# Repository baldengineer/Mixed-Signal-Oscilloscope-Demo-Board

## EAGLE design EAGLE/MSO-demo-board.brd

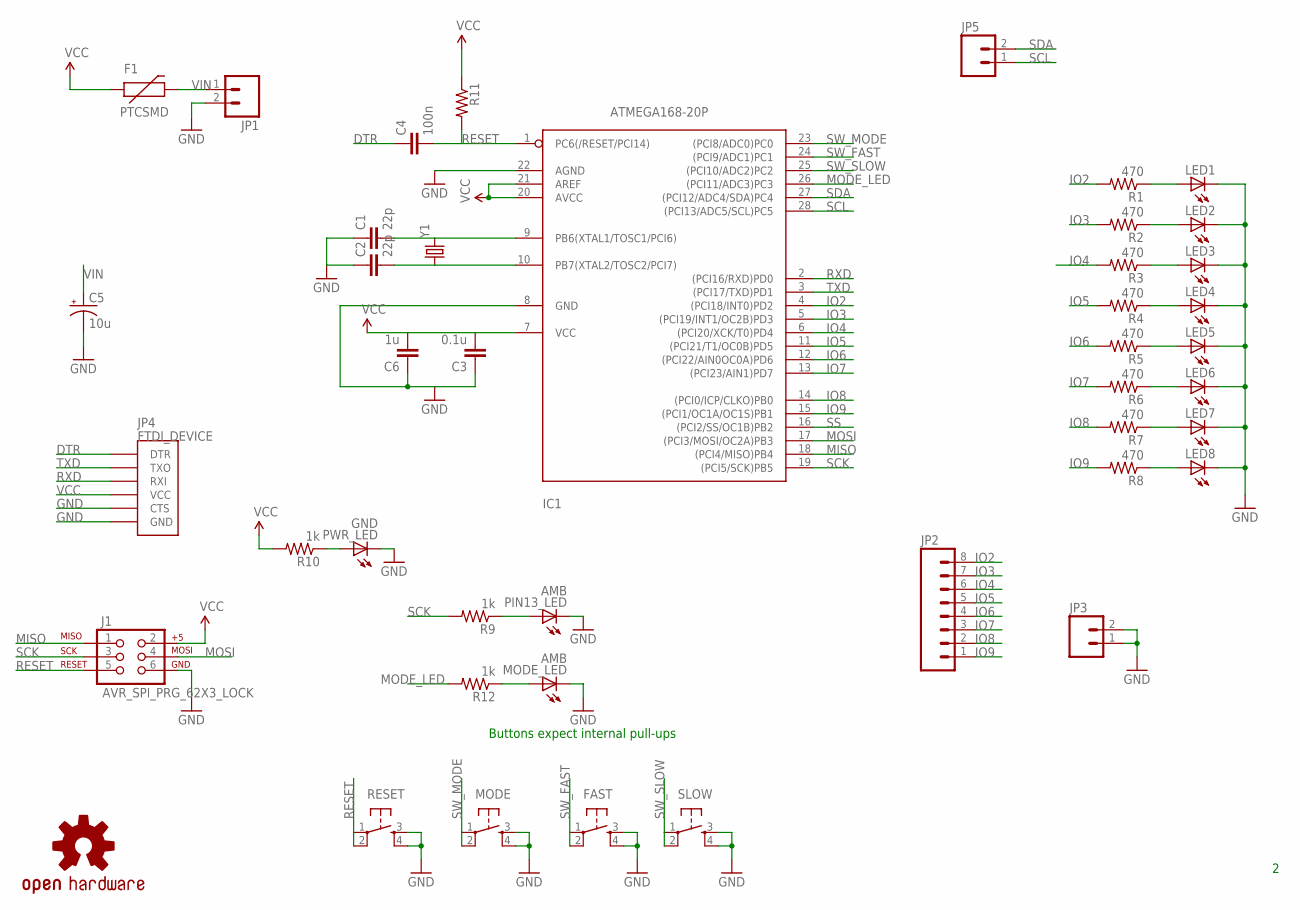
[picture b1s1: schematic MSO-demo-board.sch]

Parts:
C1, C2: 22p; 1206
C3: 0.1u; 1206
C4: 100n; 1206
C5: 10u; CT7343
C6: 1u; 1206
F1: PTCSMD; PTC-1206
FAST: TAC_SWITCHSMD; TACTILE_SWITCH_SMD
IC1: ATMEGA168-20P; DIL28-3
J1: AVR_SPI_PRG_62X3_LOCK; 2X3_LOCK
JP1, JP3, JP5: M02LOCK; 1X02_LOCK
JP2: M08LOCK; 1X08_LOCK
JP4: FTDI_DEVICE; FTDI_DEVICE_SIDE
LED1, LED2, LED3, LED4, LED5, LED6, LED7, LED8: LED1206; LED-1206
MODE: TAC_SWITCHSMD; TACTILE_SWITCH_SMD
MODE_LED: AMB; LED-1206
PIN13_LED: AMB; LED-1206
PWR_LED: GND; LED-1206
R1, R2, R3, R4, R5, R6, R7, R8: 470; 1206
R9, R10, R12: 1k; 1206
R11: RESISTOR1206; 1206
RESET: TAC_SWITCHSMD; TACTILE_SWITCH_SMD
SLOW: TAC_SWITCHSMD; TACTILE_SWITCH_SMD
U$1: OSHW-LOGOS; OSHW-LOGO-S
Y1: CRYSTALHC49UV; HC49U-V

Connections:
DTR: C4.1, JP4.P$1 (DTR)
GND: C1.1, C2.1, C3.1, C5.-, C6.1, FAST.3, FAST.4, IC1.8 (GND), IC1.22 (AGND), J1.6, JP1.2, JP3.1, JP3.2, JP4.P$5 (CTS), JP4.P$6 (GND), LED1.C, LED2.C, LED3.C, LED4.C, LED5.C, LED6.C, LED7.C, LED8.C, MODE.3, MODE.4, MODE_LED.C, PIN13_LED.C, PWR_LED.C, RESET.3, RESET.4, SLOW.3, SLOW.4
IO2: IC1.4 ((PCI18/INT0)PD2), JP2.8, R1.2
IO3: IC1.5 ((PCI19/INT1/OC2B)PD3), JP2.7, R2.2
IO4: IC1.6 ((PCI20/XCK/T0)PD4), JP2.6, R3.2
IO5: IC1.11 ((PCI21/T1/OC0B)PD5), JP2.5, R4.2
IO6: IC1.12 ((PCI22/AIN0OC0A)PD6), JP2.4, R5.2
IO7: IC1.13 ((PCI23/AIN1)PD7), JP2.3, R6.2
IO8: IC1.14 ((PCI0/ICP/CLKO)PB0), JP2.2, R7.2
IO9: IC1.15 ((PCI1/OC1A/OC1S)PB1), JP2.1, R8.2
MISO: IC1.18 ((PCI4/MISO)PB4), J1.1
MODE_LED: IC1.26 ((PCI11/ADC3)PC3), R12.2
MOSI: IC1.17 ((PCI3/MOSI/OC2A)PB3), J1.4
unnamed: PWR_LED.A, R10.1
unnamed: C1.2, IC1.9 (PB6(XTAL1/TOSC1/PCI6)), Y1.2
unnamed: C2.2, IC1.10 (PB7(XTAL2/TOSC2/PCI7)), Y1.1
unnamed: MODE_LED.A, R12.1
unnamed: PIN13_LED.A, R9.1
unnamed: LED1.A, R1.1
unnamed: LED3.A, R3.1
unnamed: LED2.A, R2.1
unnamed: LED4.A, R4.1
unnamed: LED5.A, R5.1
unnamed: LED6.A, R6.1
unnamed: LED7.A, R7.1
unnamed: LED8.A, R8.1
RESET: C4.2, IC1.1 (PC6(/RESET/PCI14)), J1.5, R11.2, RESET.1, RESET.2
RXD: IC1.2 ((PCI16/RXD)PD0), JP4.P$3 (RXI)
SCK: IC1.19 ((PCI5/SCK)PB5), J1.3, R9.2
SCL: IC1.28 ((PCI13/ADC5/SCL)PC5), JP5.1
SDA: IC1.27 ((PCI12/ADC4/SDA)PC4), JP5.2
SS: IC1.16 ((PCI2/SS/OC1B)PB2)
SW_FAST: FAST.1, FAST.2, IC1.24 ((PCI9/ADC1)PC1)
SW_MODE: IC1.23 ((PCI8/ADC0)PC0), MODE.1, MODE.2
SW_SLOW: IC1.25 ((PCI10/ADC2)PC2), SLOW.1, SLOW.2
TXD: IC1.3 ((PCI17/TXD)PD1), JP4.P$2 (TXO)
VCC: C3.2, C6.2, F1.1, IC1.7 (VCC), IC1.20 (AVCC), IC1.21 (AREF), J1.2, JP4.P$4 (VCC), R10.2, R11.1
VIN: C5.+, F1.2, JP1.1

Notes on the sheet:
Buttons expect internal pull-ups

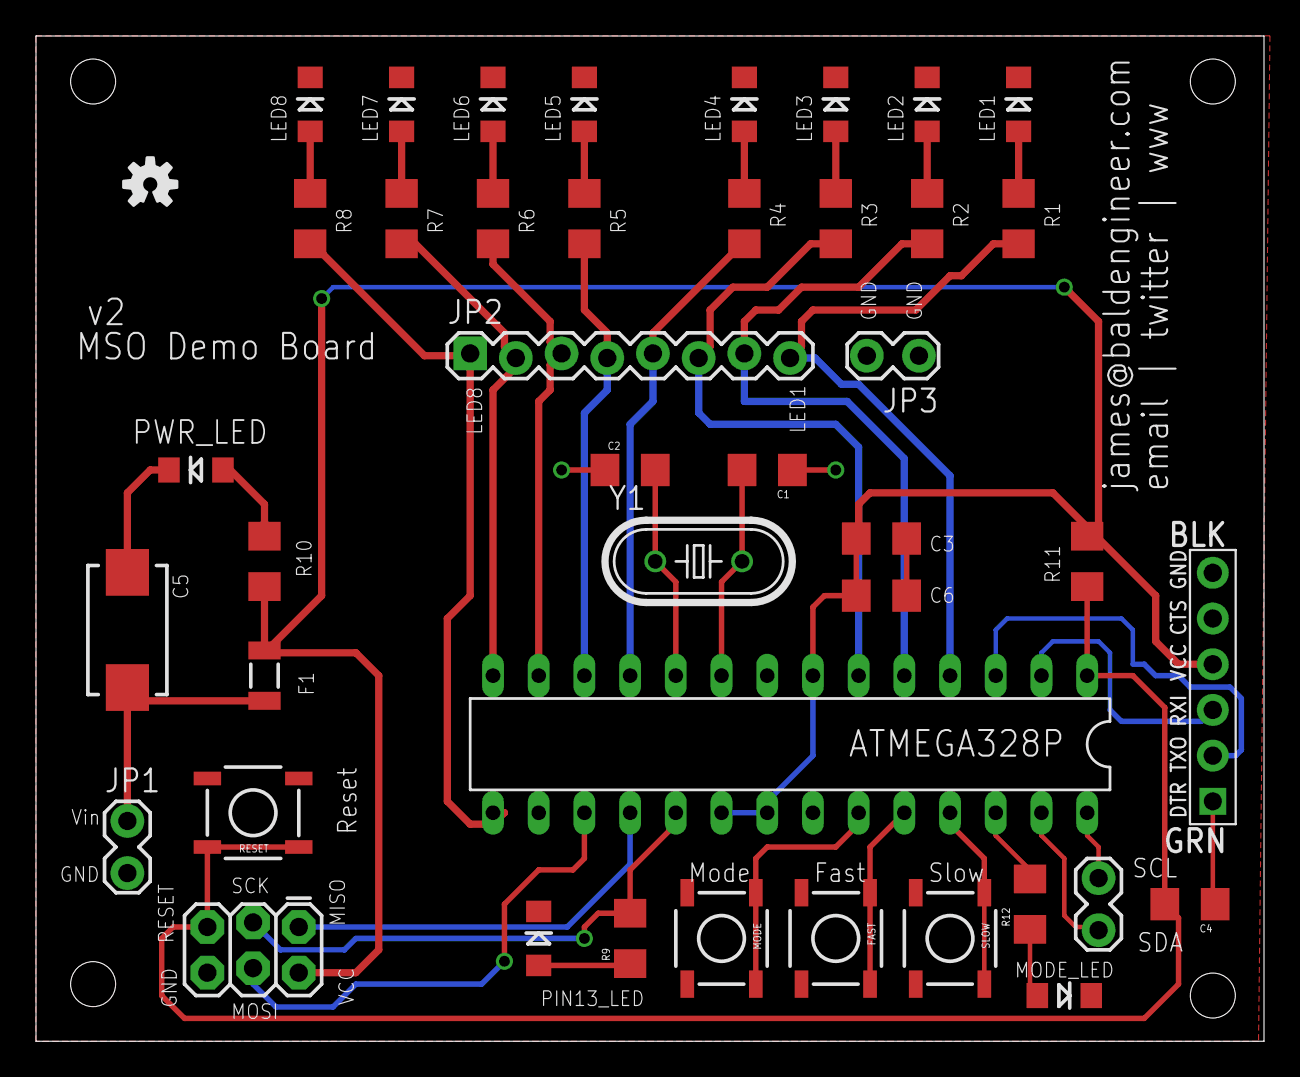
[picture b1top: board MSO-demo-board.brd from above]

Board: 2 copper layers, 68.2 x 55.9 mm, 43 parts (0 on the bottom side), 37 nets.

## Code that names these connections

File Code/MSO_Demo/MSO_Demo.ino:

#define ON true
#define OFF false

const byte sw_mode = A0;
const byte sw_fast = A1;
const byte sw_slow = A2;
const byte mode_led = A3;

boolean previous_mode = HIGH;
boolean previous_fast = HIGH;
boolean previous_slow = HIGH;
boolean mode_led_state = false;

byte counter=0;
int delayTime = 50;
boolean enableError = false;
boolean errorRunning = false;
boolean errorState = OFF;
boolean displayError = false;

unsigned long incrementCounter = 0;
unsigned long errorTimeOut = 100;
unsigned long endOfError = 0;
boolean showNewTime = false;

void setup() {
  // put your setup code here, to run once:
  Serial.begin(9600);
  for(int i=0; i<8; i++)
    pinMode(i+2, OUTPUT);
  pinMode(13, OUTPUT);
  
  pinMode(sw_mode, INPUT_PULLUP); //MODE
  pinMode(sw_fast, INPUT_PULLUP); // FAST
  pinMode(sw_slow, INPUT_PULLUP); // SLOW
  pinMode(mode_led, OUTPUT);  // LED
  
  randomSeed(analogRead(A4));
}

void loop() {
  // put your main code here, to run repeatedly: 
  digitalWrite(mode_led, mode_led_state);
  processButtons();
  
  while (Serial.available())
    processSerial();


  if (showNewTime) printTime();

  if ((unsigned long)(millis() - incrementCounter) >= delayTime) {
    counter++;
//    incrementCounter = millis() + delayTime;
    incrementCounter = incrementCounter + delayTime; 
  }
  checkError();
  if (displayError) bitWrite(counter,1,1);

  for(int i=0; i<8; i++) {
    digitalWrite(i+2, bitRead(counter,i));
  }
//  delay(delayTime);
}

void checkError() {
  // if the global enable is off, don't do anything.
  if (enableError == false) {
    displayError = false;
    return;
  }
  
  digitalWrite(13, errorState);
  
  if (errorState == ON) {
     // leave the bit high for errorTimeOut
     if ((unsigned long)(millis() - endOfError) >= errorTimeOut) {
        // it's done
       errorState = OFF;
       endOfError = endOfError + errorTimeOut;
       displayError = false;
       analogWrite(11, 0);
     }
  } else {
       // leave the bit low for errorTimeOut
     if ((unsigned long)(millis() - endOfError) >= errorTimeOut) {
        // it's done
       errorState = ON;
       endOfError = endOfError + errorTimeOut;
       displayError = true;
       analogWrite(11, random(64,192));
     }
  }
}
void printTime() {
  Serial.print(delayTime);
  Serial.print(" - ");
  if (enableError) 
    Serial.print("Error On");
  else
    Serial.print("Error Off");
  Serial.println();
  showNewTime = false; 
}

/*
const byte sw_mode = A0;
const byte sw_fast = A1;
const byte sw_slow = A2;
const byte mode_led = A3;

boolean previous_mode = HIGH;
boolean previous_fast = HIGH;
boolean previous_slow = HIGH;
boolean mode_led_state = FALSE;
*/

void processButtons() {
  boolean current_mode = digitalRead(sw_mode);
  boolean current_fast = digitalRead(sw_fast);
  boolean current_slow = digitalRead(sw_slow);
  
  if ((previous_mode == HIGH) && (current_mode == LOW)) {
    enableError = !enableError;
    mode_led_state = enableError;
    showNewTime = true; 
  }
  
  if ((previous_fast == HIGH) && (current_fast == LOW)) {
    delayTime -= 10;
    showNewTime = true;
  }
  
  if ((previous_slow == HIGH) && (current_slow == LOW)) {
    delayTime += 10;
    showNewTime = true;
  }
  
  checkDelayBounds();
  
  
  previous_mode = current_mode;
  previous_fast = current_fast;
  previous_slow = current_slow;
}

void checkDelayBounds() {
    if (delayTime <= 0) delayTime = 1;
    if (delayTime >= 1000) delayTime = 1000; 
}

void processSerial() {
  int incoming = Serial.read();

  if (incoming == '!')
    enableError = !enableError;

  if (incoming == '+')
    delayTime += 10;

  if (incoming == '-')
    delayTime -= 10;

  checkDelayBounds();

  showNewTime = true;
  delay(1); //add a little more time to give another character a chance to arrive.
}

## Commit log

2013-08-26 Initial Commit
    Arduino Code and EAGLE R1 board.
2013-08-26 Arduino IDE moved the file...
    …sigh.
2013-09-24 Added support for push buttons
    new pcb has push buttons, added support for them
2013-09-24 deleting...
2013-09-24 Fixed VCC Grounded mistake
    AVCC was tied to ground causing a short at power up. Tied AVCC and
    AREF to 5V instead of ground. Also swapped TX and RX on FTDI pinout
    (was backwards)

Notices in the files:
parts and their libraries:
SparkFun: Licensing: CC v3.0 Share-Alike You are welcome to use this library for commercial purposes.
